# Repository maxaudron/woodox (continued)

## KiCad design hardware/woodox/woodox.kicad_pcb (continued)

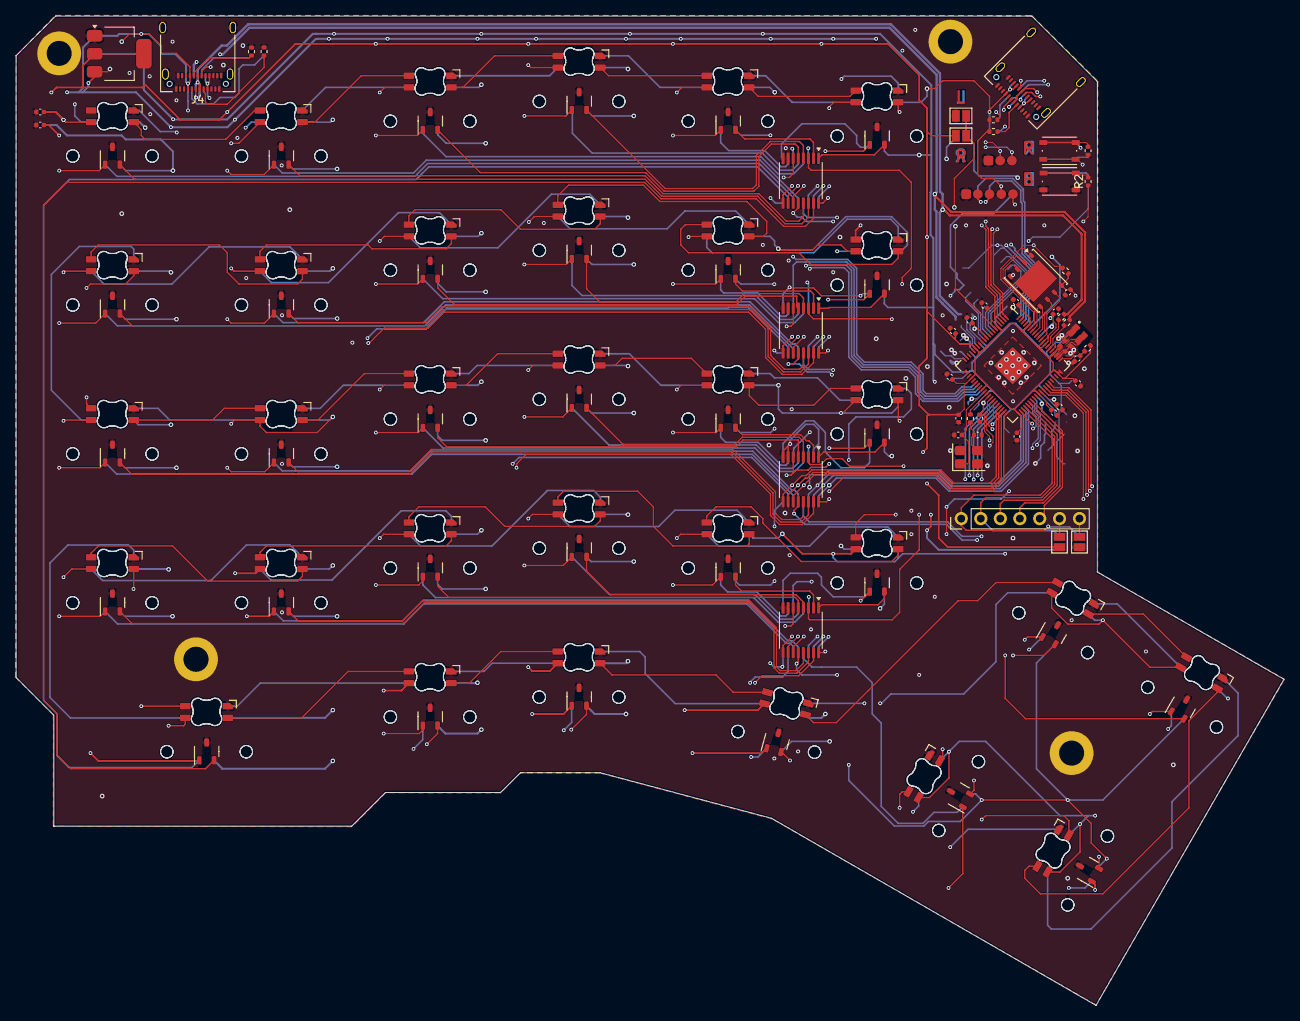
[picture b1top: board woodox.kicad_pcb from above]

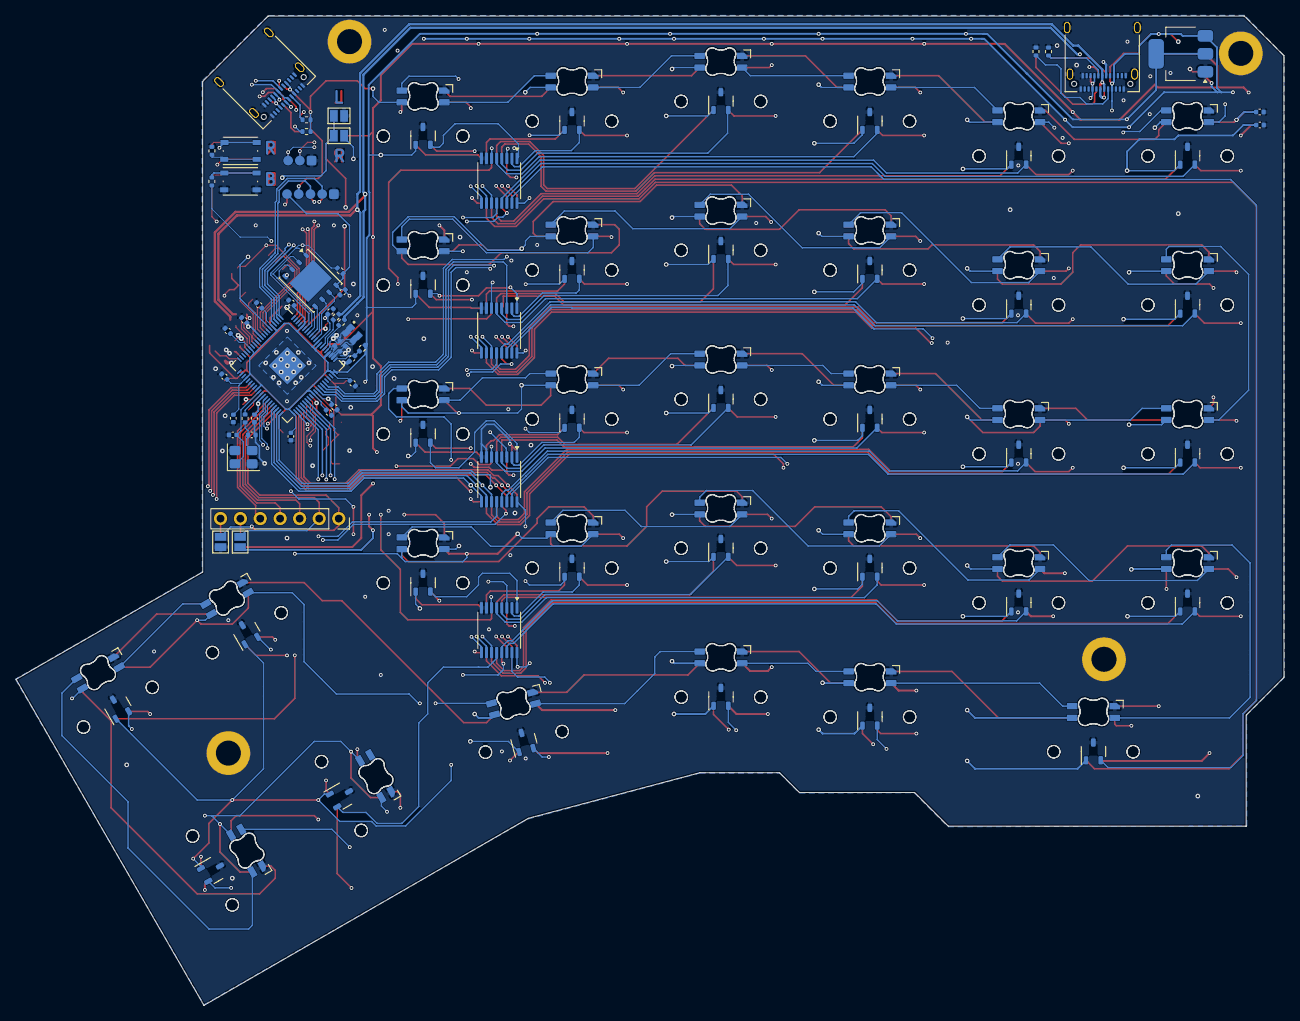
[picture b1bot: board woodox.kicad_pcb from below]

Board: 4 copper layers, 162.2 x 126.5 mm, 233 parts (114 on the bottom side), 210 nets.

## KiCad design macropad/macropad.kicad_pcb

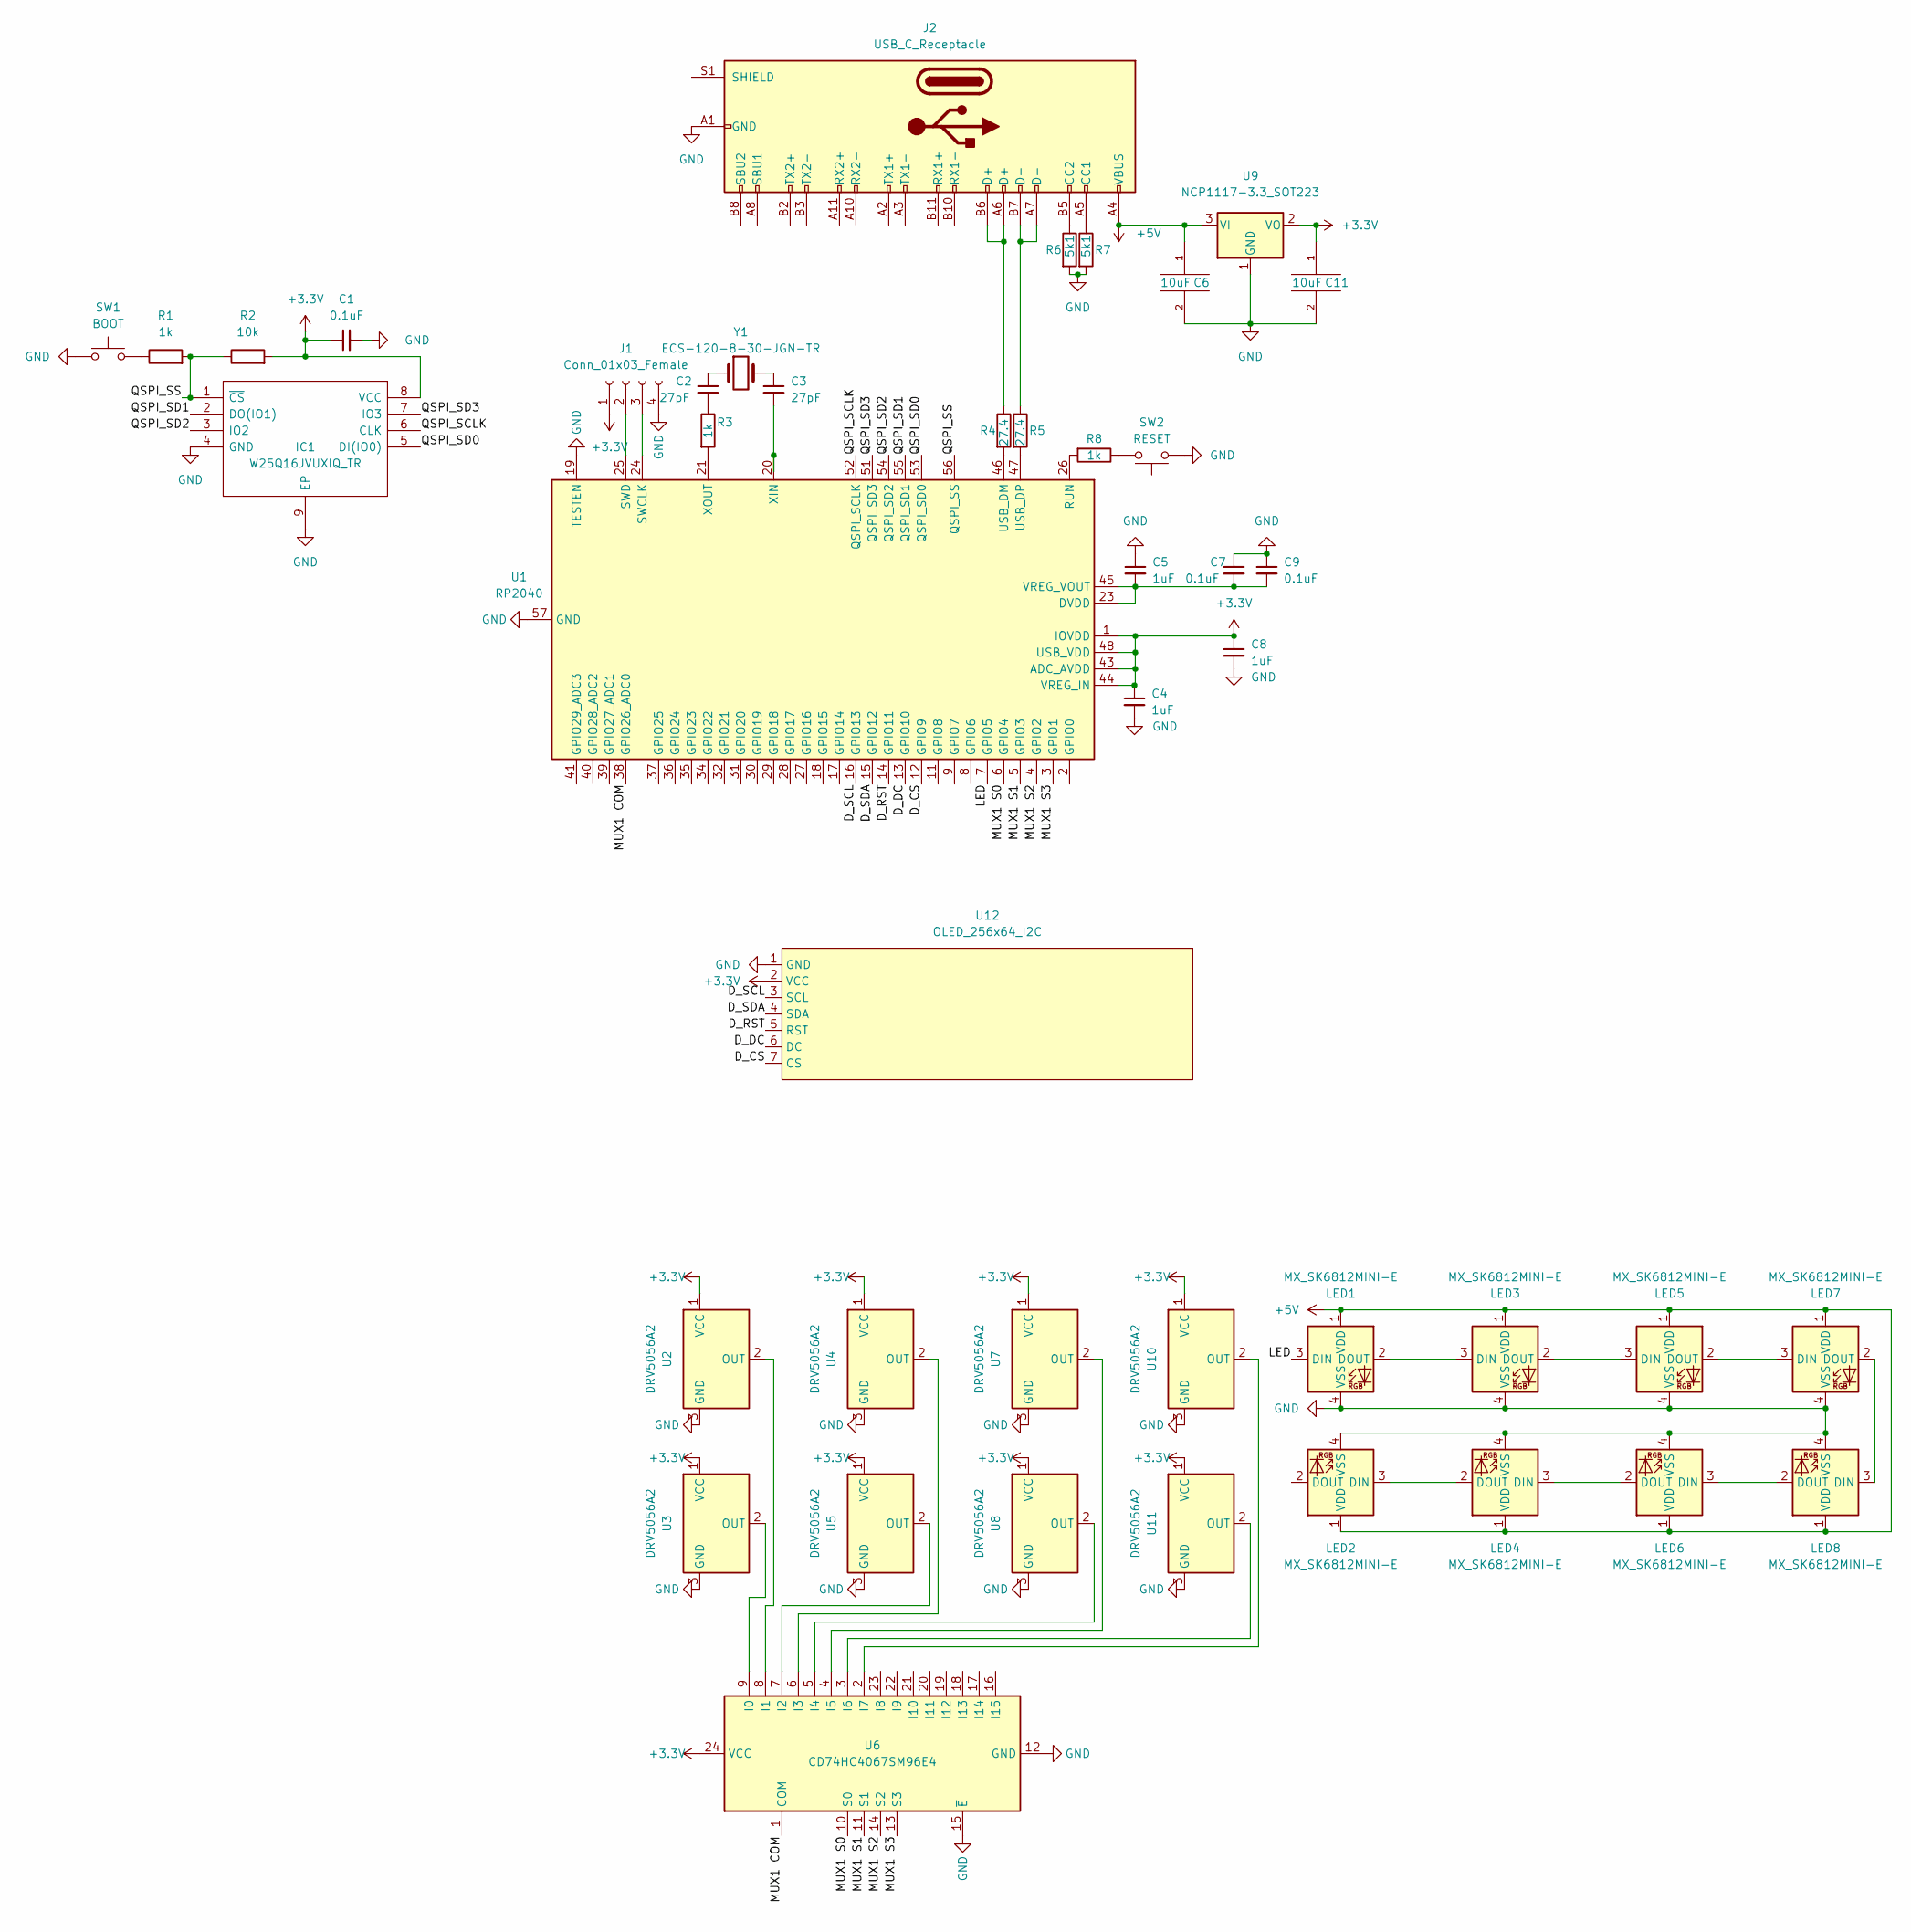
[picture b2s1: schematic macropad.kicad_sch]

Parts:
C1, C7, C9: 0.1uF; C_0603_1608Metric; MPN MSAST105SB7104KFNB25
C2, C3: 27pF; C_0603_1608Metric; MPN GJM1555C1H270FB01D
C4, C5, C8: 1uF; C_0603_1608Metric; MPN MAASA105CD7105KFCA01
C6, C11: 10uF; C_0603_1608Metric; MPN GRM155R60J106ME15D
IC1: W25Q16JVUXIQ_TR; SON50P300X200X60-9N; Mouser Part Number 454-W25Q16JVUXIQTR
J1: Conn_01x03_Female; PinHeader_1x04_P2.54mm_Vertical
J2: USB_C_Receptacle; USB_C_Receptacle_Amphenol_12401610E4-2A; MPN 12401832E402A
LED1, LED3, LED5, LED7: MX_SK6812MINI-E; LED_MX_SK6812MINI-R; MPN SK6812MINI-E
LED2, LED4, LED6, LED8: MX_SK6812MINI-E; LED_MX_SK6812MINI-R_FLIPPED; MPN SK6812MINI-E
R1, R3, R8: 1k; R_0603_1608Metric; MPN RCC06031K00FKEA
R2: 10k; R_0603_1608Metric; MPN ERJ-3EKF1002V
R4, R5: 27.4; R_0603_1608Metric; MPN CRCW060327R4FKEB
R6, R7: 5k1; R_0603_1608Metric; MPN ERJ-3EKF5101V
SW1: BOOT; SW_Push_1P1T_NO_Vertical_Wuerth_434133025816; MPN 95C06B2GWRT
SW2: RESET; SW_Push_1P1T_NO_Vertical_Wuerth_434133025816; MPN 95C06B2GWRT
U1: RP2040; QFN-56-1EP_7x7mm_P0.4mm_EP3.2x3.2mm; MPN RPI Chip RP2040-7-500
U2, U3, U4, U5, U7, U8, U10, U11: DRV5056A2; DRV505x; MPN DRV5056A2QDBZT
U6: CD74HC4067SM96E4; SSOP-24_5.3x8.2mm_P0.65mm; MPN CD74HC4067SM96E4
U9: NCP1117-3.3_SOT223; SOT-223-3_TabPin2; MPN NCP1117LPST33T3G
U12: OLED_256x64_I2C
Y1: ECS-120-8-30-JGN-TR; Crystal_SMD_5032-2Pin_5.0x3.2mm; MPN ECS-120-8-30-JGN-TR

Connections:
+3.3V: C1.1, C4.1, C8.1, C11.1, IC1.8 (VCC), J1.1, R2.2, U1.1 (IOVDD), U1.10 (IOVDD), U1.22 (IOVDD), U1.33 (IOVDD), U1.42 (IOVDD), U1.43 (ADC_AVDD), U1.44 (VREG_IN), U1.48 (USB_VDD), U1.49 (IOVDD), U2.1 (VCC), U3.1 (VCC), U4.1 (VCC), U5.1 (VCC), U6.24 (VCC), U7.1 (VCC), U8.1 (VCC), U9.2 (VO), U10.1 (VCC), U11.1 (VCC), U12.2 (VCC)
+5V: C6.1, J2.A4 (VBUS), J2.A9 (VBUS), J2.B4 (VBUS), J2.B9 (VBUS), LED1.1 (VDD), LED2.1 (VDD), LED3.1 (VDD), LED4.1 (VDD), LED5.1 (VDD), LED6.1 (VDD), LED7.1 (VDD), LED8.1 (VDD), U9.3 (VI)
/D_CS: U1.12 (GPIO9), U12.7 (CS)
/D_DC: U1.13 (GPIO10), U12.6 (DC)
/D_RST: U1.14 (GPIO11), U12.5 (RST)
/D_SCL: U1.16 (GPIO13), U12.3 (SCL)
/D_SDA: U1.15 (GPIO12), U12.4 (SDA)
/LED: LED1.3 (DIN), U1.7 (GPIO5)
/MUX1 COM: U1.38 (GPIO26_ADC0), U6.1 (COM)
/MUX1 S0: U1.6 (GPIO4), U6.10 (S0)
/MUX1 S1: U1.5 (GPIO3), U6.11 (S1)
/MUX1 S2: U1.4 (GPIO2), U6.14 (S2)
/MUX1 S3: U1.3 (GPIO1), U6.13 (S3)
/QSPI_SCLK: IC1.6 (CLK), U1.52 (QSPI_SCLK)
/QSPI_SD0: IC1.5 (DI(IO0)), U1.53 (QSPI_SD0)
/QSPI_SD1: IC1.2 (DO(IO1)), U1.55 (QSPI_SD1)
/QSPI_SD2: IC1.3 (IO2), U1.54 (QSPI_SD2)
/QSPI_SD3: IC1.7 (IO3), U1.51 (QSPI_SD3)
/QSPI_SS: IC1.1 (~CS), R1.2, R2.1, U1.56 (QSPI_SS)
GND: C1.2, C4.2, C5.1, C6.2, C7.1, C8.2, C9.1, C11.2, IC1.4 (GND), IC1.9 (EP), J1.4, J2.A1 (GND), J2.A12 (GND), J2.B1 (GND), J2.B12 (GND), LED1.4 (VSS), LED2.4 (VSS), LED3.4 (VSS), LED4.4 (VSS), LED5.4 (VSS), LED6.4 (VSS), LED7.4 (VSS), LED8.4 (VSS), R6.2, R7.2, SW1.1, SW2.1, U1.19 (TESTEN), U1.57 (GND), U2.3 (GND), U3.3 (GND), U4.3 (GND), U5.3 (GND), U6.12 (GND), U6.15 (~E), U7.3 (GND), U8.3 (GND), U9.1 (GND), U10.3 (GND), U11.3 (GND), U12.1 (GND)
unnamed: C2.1, Y1.1
unnamed: C2.2, R3.1
unnamed: C3.1, Y1.2
unnamed: J1.2, U1.25 (SWD)
unnamed: J1.3, U1.24 (SWCLK)
unnamed: J2.A5 (CC1), R7.1
unnamed: J2.B5 (CC2), R6.1
unnamed: LED1.2 (DOUT), LED3.3 (DIN)
unnamed: LED2.3 (DIN), LED4.2 (DOUT)
unnamed: LED3.2 (DOUT), LED5.3 (DIN)
unnamed: LED4.3 (DIN), LED6.2 (DOUT)
unnamed: LED5.2 (DOUT), LED7.3 (DIN)
unnamed: LED6.3 (DIN), LED8.2 (DOUT)
unnamed: LED7.2 (DOUT), LED8.3 (DIN)
unnamed: R1.1, SW1.2
unnamed: R8.1, SW2.2
unnamed: R8.2, U1.26 (RUN)
unnamed: R4.2, U1.46 (USB_DM)
unnamed: R5.2, U1.47 (USB_DP)
unnamed: C5.2, C7.2, C9.2, U1.23 (DVDD), U1.45 (VREG_VOUT), U1.50 (DVDD)
unnamed: C3.2, U1.20 (XIN)
unnamed: R3.2, U1.21 (XOUT)
unnamed: U2.2 (OUT), U6.8 (I1)
unnamed: U3.2 (OUT), U6.9 (I0)
unnamed: U4.2 (OUT), U6.6 (I3)
unnamed: U5.2 (OUT), U6.7 (I2)
unnamed: U6.5 (I4), U8.2 (OUT)
unnamed: U6.4 (I5), U7.2 (OUT)
unnamed: U6.2 (I7), U10.2 (OUT)
unnamed: U6.3 (I6), U11.2 (OUT)

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
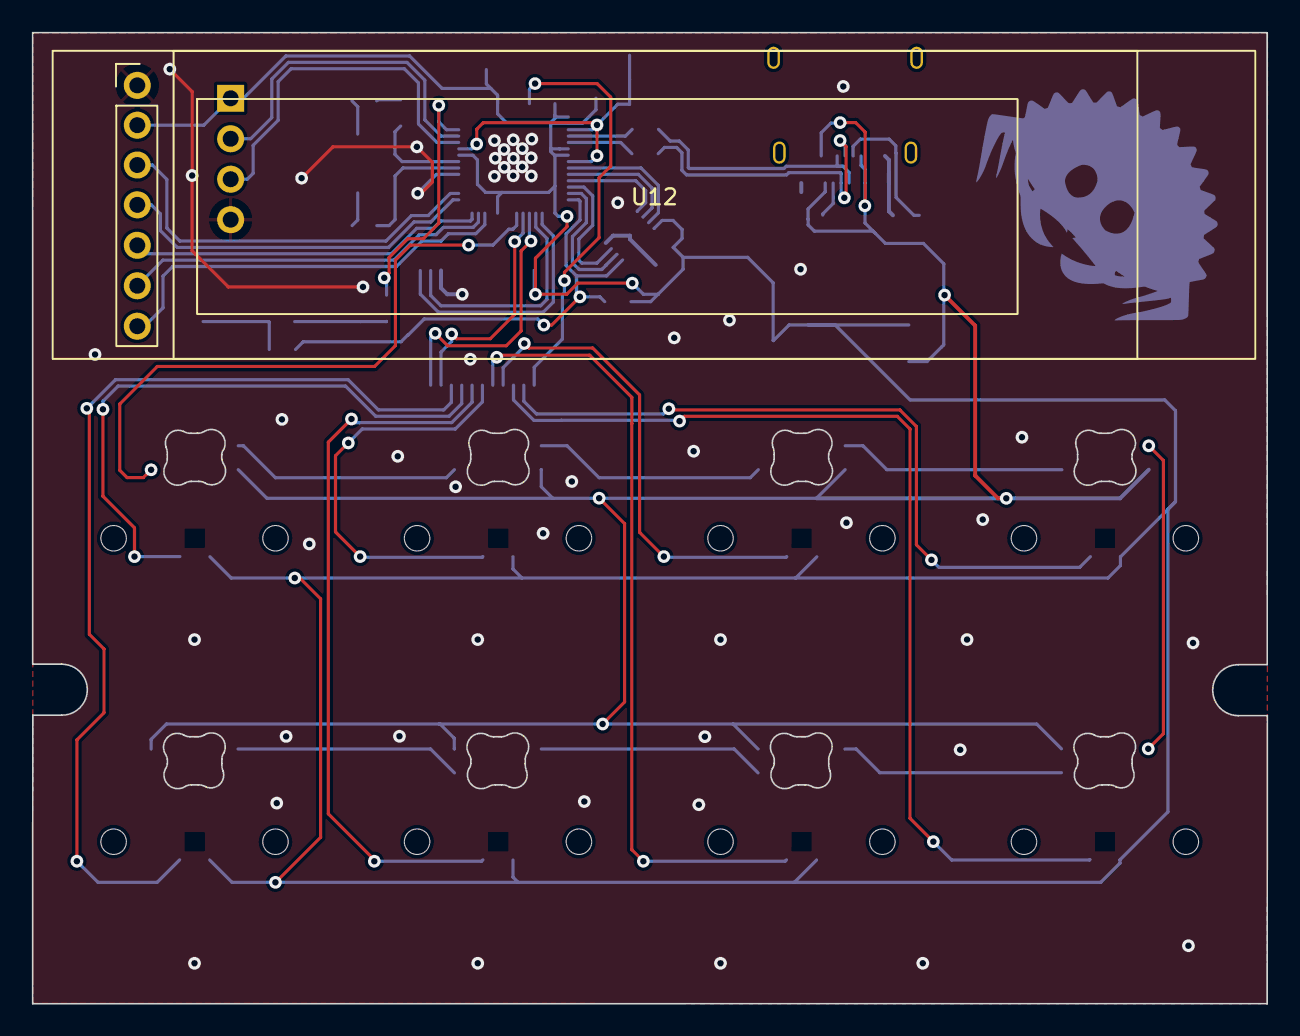
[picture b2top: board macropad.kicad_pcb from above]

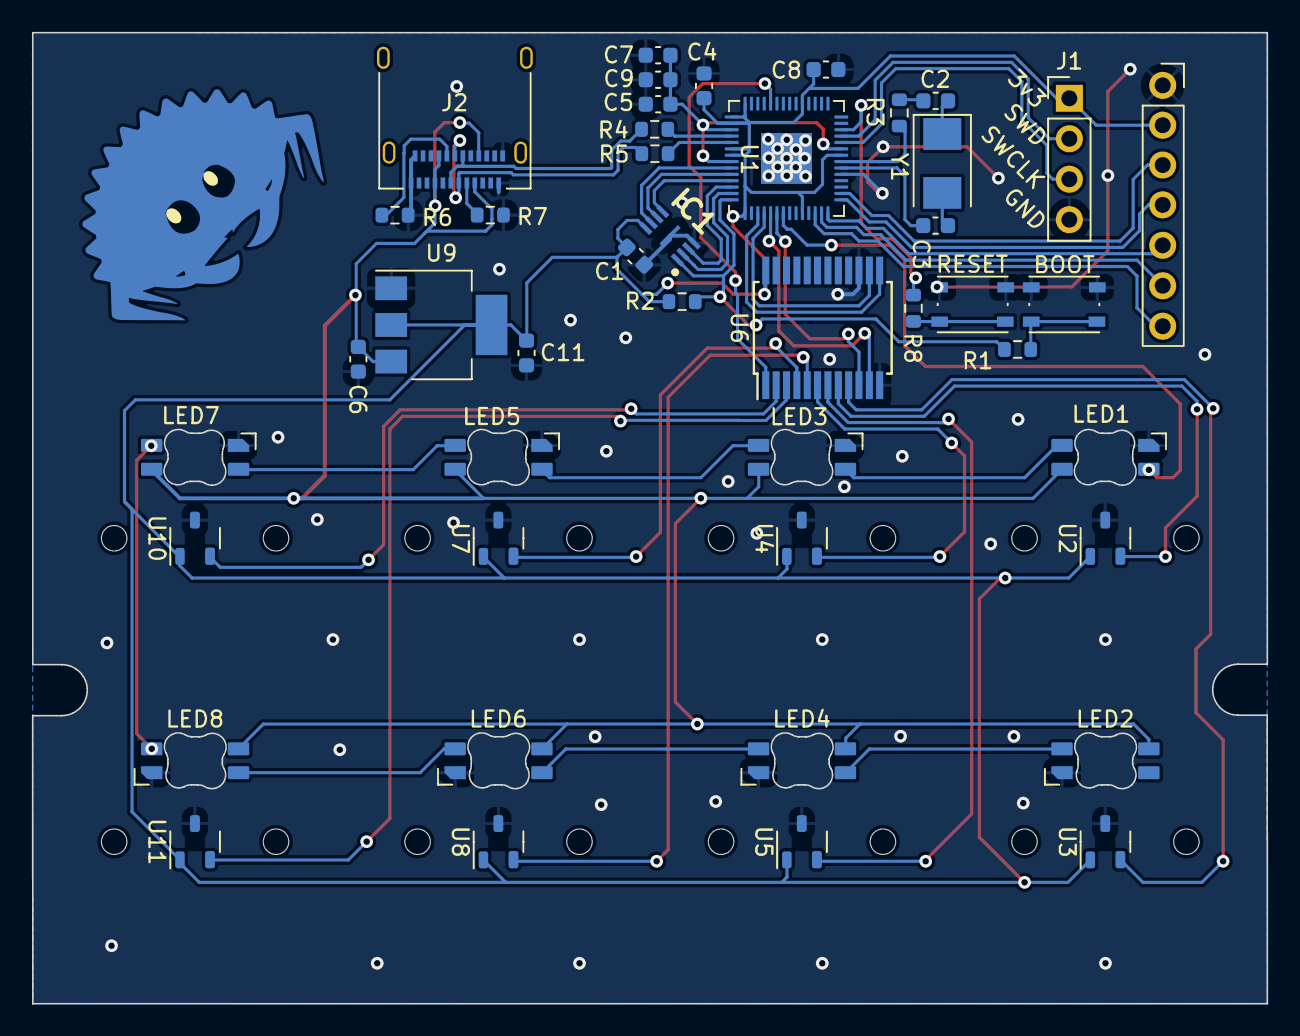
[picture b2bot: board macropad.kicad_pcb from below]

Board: 2 copper layers, 77.5 x 61.0 mm, 44 parts (43 on the bottom side), 52 nets.

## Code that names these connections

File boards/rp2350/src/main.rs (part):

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        Clock,
        gpio::{
            FunctionUart, Pin, PullDown,
            bank0::{Gpio4, Gpio5},
        },
        pac::UART1,
        uart::{UartDevice, ValidUartPinout},
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        uart: Uart<
            UART1,
            (
                Pin<Gpio4, FunctionUart, PullDown>,
                Pin<Gpio5, FunctionUart, PullDown>,
            ),
        >,
        #[lock_free]
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}

hal::bsp_pins!(
    Gpio32 { name: mux_enable },
    Gpio31 { name: mux_s0 },
    Gpio30 { name: mux_s1 },
    Gpio29 { name: mux_s2 },
    Gpio33 { name: led },
    Gpio44 { name: mux1_com },
    Gpio43 { name: mux2_com },
    Gpio42 { name: mux3_com },
    Gpio41 { name: mux4_com },
    Gpio34 { name: d_cs },
    Gpio35 { name: d_dc },
    Gpio36 { name: d_rst },
    Gpio37 { name: d_sda },
    Gpio38 { name: d_scl },
    Gpio4 { name: i2c_sda },
    Gpio5 { name: i2c_sdl },
    Gpio6 { name: i2c_sda_acc },
    Gpio7 { name: i2c_sdl_acc },
    Gpio8 { name: handedness },
);

/// Program metadata for `picotool info`
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
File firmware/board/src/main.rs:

#![no_std]
#![no_main]

use hal::multicore::Multicore;
use hal::multicore::Stack;
use rp2040_hal as hal;
use usb_device::class_prelude::*;

use defmt::*;
use defmt_rtt as _;
use panic_probe as _;

use hal::{clocks, entry, pac, watchdog, Adc};

mod hardware;
mod scan;
mod usb;

use woodox_lib::layout;

/// The linker will place this boot block at the start of our program image. We
/// need this to help the ROM bootloader get our code up and running.
#[link_section = ".boot2"]
#[used]
pub static BOOT2: [u8; 256] = rp2040_boot2::BOOT_LOADER_GENERIC_03H;

pub const DMA_BUF_SIZE: usize = 4;

static mut CORE1_STACK: Stack<4096> = Stack::new();

#[entry]
fn main() -> ! {
    info!("program start");

    // ------------------------------------
    // Setup core hardware
    let mut pac = pac::Peripherals::take().unwrap();
    let _core = pac::CorePeripherals::take().unwrap();
    let mut watchdog = watchdog::Watchdog::new(pac.WATCHDOG);
    let mut sio = hal::Sio::new(pac.SIO);

    // External high-speed crystal on the pico board is 12Mhz
    let external_xtal_freq_hz = 12_000_000u32;
    let clocks = clocks::init_clocks_and_plls(
        external_xtal_freq_hz,
        pac.XOSC,
        pac.CLOCKS,
        pac.PLL_SYS,
        pac.PLL_USB,
        &mut pac.RESETS,
        &mut watchdog,
    )
    .ok()
    .unwrap();

    #[allow(unused_variables)]
    let timer = hal::Timer::new(pac.TIMER, &mut pac.RESETS);

    let pins = Pins::new(
        pac.IO_BANK0,
        pac.PADS_BANK0,
        sio.gpio_bank0,
        &mut pac.RESETS,
    );

    info!("core initialization finished");

    // ------------------------------------
    // Setup Mux and ADC for switch scanning

    // Initialize MUX
    let mux = hardware::CD74HC4067::new(
        pins.mux1_s0.into_push_pull_output(),
        pins.mux1_s1.into_push_pull_output(),
        pins.mux1_s2.into_push_pull_output(),
        pins.mux1_s3.into_push_pull_output(),
    );

    // Initialize ADC
    let adc = {
        let adc = Adc::new(pac.ADC, &mut pac.RESETS);
        let _adc_pin_0 = pins.mux1_com.into_floating_input();
        let _adc_pin_1 = pins.mux2_com.into_floating_input();
        let _adc_pin_2 = pins.mux3_com.into_floating_input();
        let _adc_pin_3 = pins.mux4_com.into_floating_input();

        let adc = adc.free();
        adc.cs.modify(|_, w| unsafe { w.rrobin().bits(0b01111) });

        adc.cs.modify(|_, w| unsafe { w.ainsel().bits(0) });
        adc.cs.modify(|_, w| w.en().set_bit());
        while !adc.cs.read().ready().bit_is_set() {
            cortex_m::asm::nop();
        }

        info!("adc initialization finished");

        adc
    };

    // ------------------------------------
    // Setup USB BUS
    let usb_bus = UsbBusAllocator::new(hal::usb::UsbBus::new(
        pac.USBCTRL_REGS,
        pac.USBCTRL_DPRAM,
        clocks.usb_clock,
        true,
        &mut pac.RESETS,
    ));

    // ------------------------------------
    // Start switch scan loop on core 1
    let mut mc = Multicore::new(&mut pac.PSM, &mut pac.PPB, &mut sio.fifo);
    let cores = mc.cores();
    let core1 = &mut cores[1];
    let _scan = core1.spawn(unsafe { &mut CORE1_STACK.mem }, || scan::scan(adc, mux));

    // ------------------------------------
    // Start usb controlelr loop on core 0
    usb::usb::<hal::usb::UsbBus>(timer, usb_bus)
}

hal::bsp_pins!(
    Gpio0 { name: pull_up },
    Gpio1 { name: mux1_s3 },
    Gpio2 { name: mux1_s2 },
    Gpio3 { name: mux1_s1 },
    Gpio4 { name: mux1_s0 },
    Gpio5 { name: led },
    Gpio26 { name: mux1_com },
    Gpio27 { name: mux2_com },
    Gpio28 { name: mux3_com },
    Gpio29 { name: mux4_com },
    // Gpio9 { name: d_cs },
    Gpio10 { name: d_dc },
    Gpio11 { name: d_rst },
    Gpio12 { name: d_sda },
    Gpio13 { name: d_scl },
);

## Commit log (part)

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2022-12-30 init
2023-01-02 finish left hand pcb
2023-02-18 finish macropad pcb
2023-02-18 rust project scaffold
2023-03-06 fix multiple issues with macropad pcb
2023-03-06 dma and adc schenanigans
2023-03-07 implement basic scanning
2023-03-11 flip usb data lines to correct orientation
2023-03-12 reorganize firmware and finish base keymap impl
2023-03-12 add support for keymap options without parenthesis
2023-03-12 add layer transparency
2023-03-24 add layertap and grvesc
2023-03-24 rework macropad usb data lines
2023-03-24 finish impl of LayerTap key
2023-03-24 impl KeyTap and extend documentation
2023-04-06 implement rapid trigger
2023-04-06 fixup! docs
2026-03-07 whatever the fuck i all did
2026-03-31 redox woodox left hand pcb
2026-03-31 cleanup pcb
2026-04-01 double sided pcb
2026-04-01 usb-c interconnects and expansion solder pads
2026-04-01 pcb images
2026-04-02 rp2350 redesign
2026-04-02 fix lints
2026-04-03 mounting holes
2026-04-03 misc fix
2026-05-11 update firmware scaffold
2026-05-14 update firmware deps & fixup
2026-05-16 pre-reorganize stash
2026-05-16 reorganize file structure
2026-05-18 rp2350 changes
2026-05-24 start redesign pre rtic
2026-05-25 redo main scan & usb loop with rtic
2026-05-25 usb timers
2026-06-05 reworked keymap/keyboard state and switch calucations
2026-06-08 !wip test hall sensors
2026-06-11 unfuck and test a bunch of sensor stuff
2026-06-13 review switch tests and fix rapid trigger
2026-06-13 invert switch distance logic to use compression travel
2026-06-14 fix dma buffer mux mapping not being consistent
2026-06-17 fix stupid default switch trig limits
